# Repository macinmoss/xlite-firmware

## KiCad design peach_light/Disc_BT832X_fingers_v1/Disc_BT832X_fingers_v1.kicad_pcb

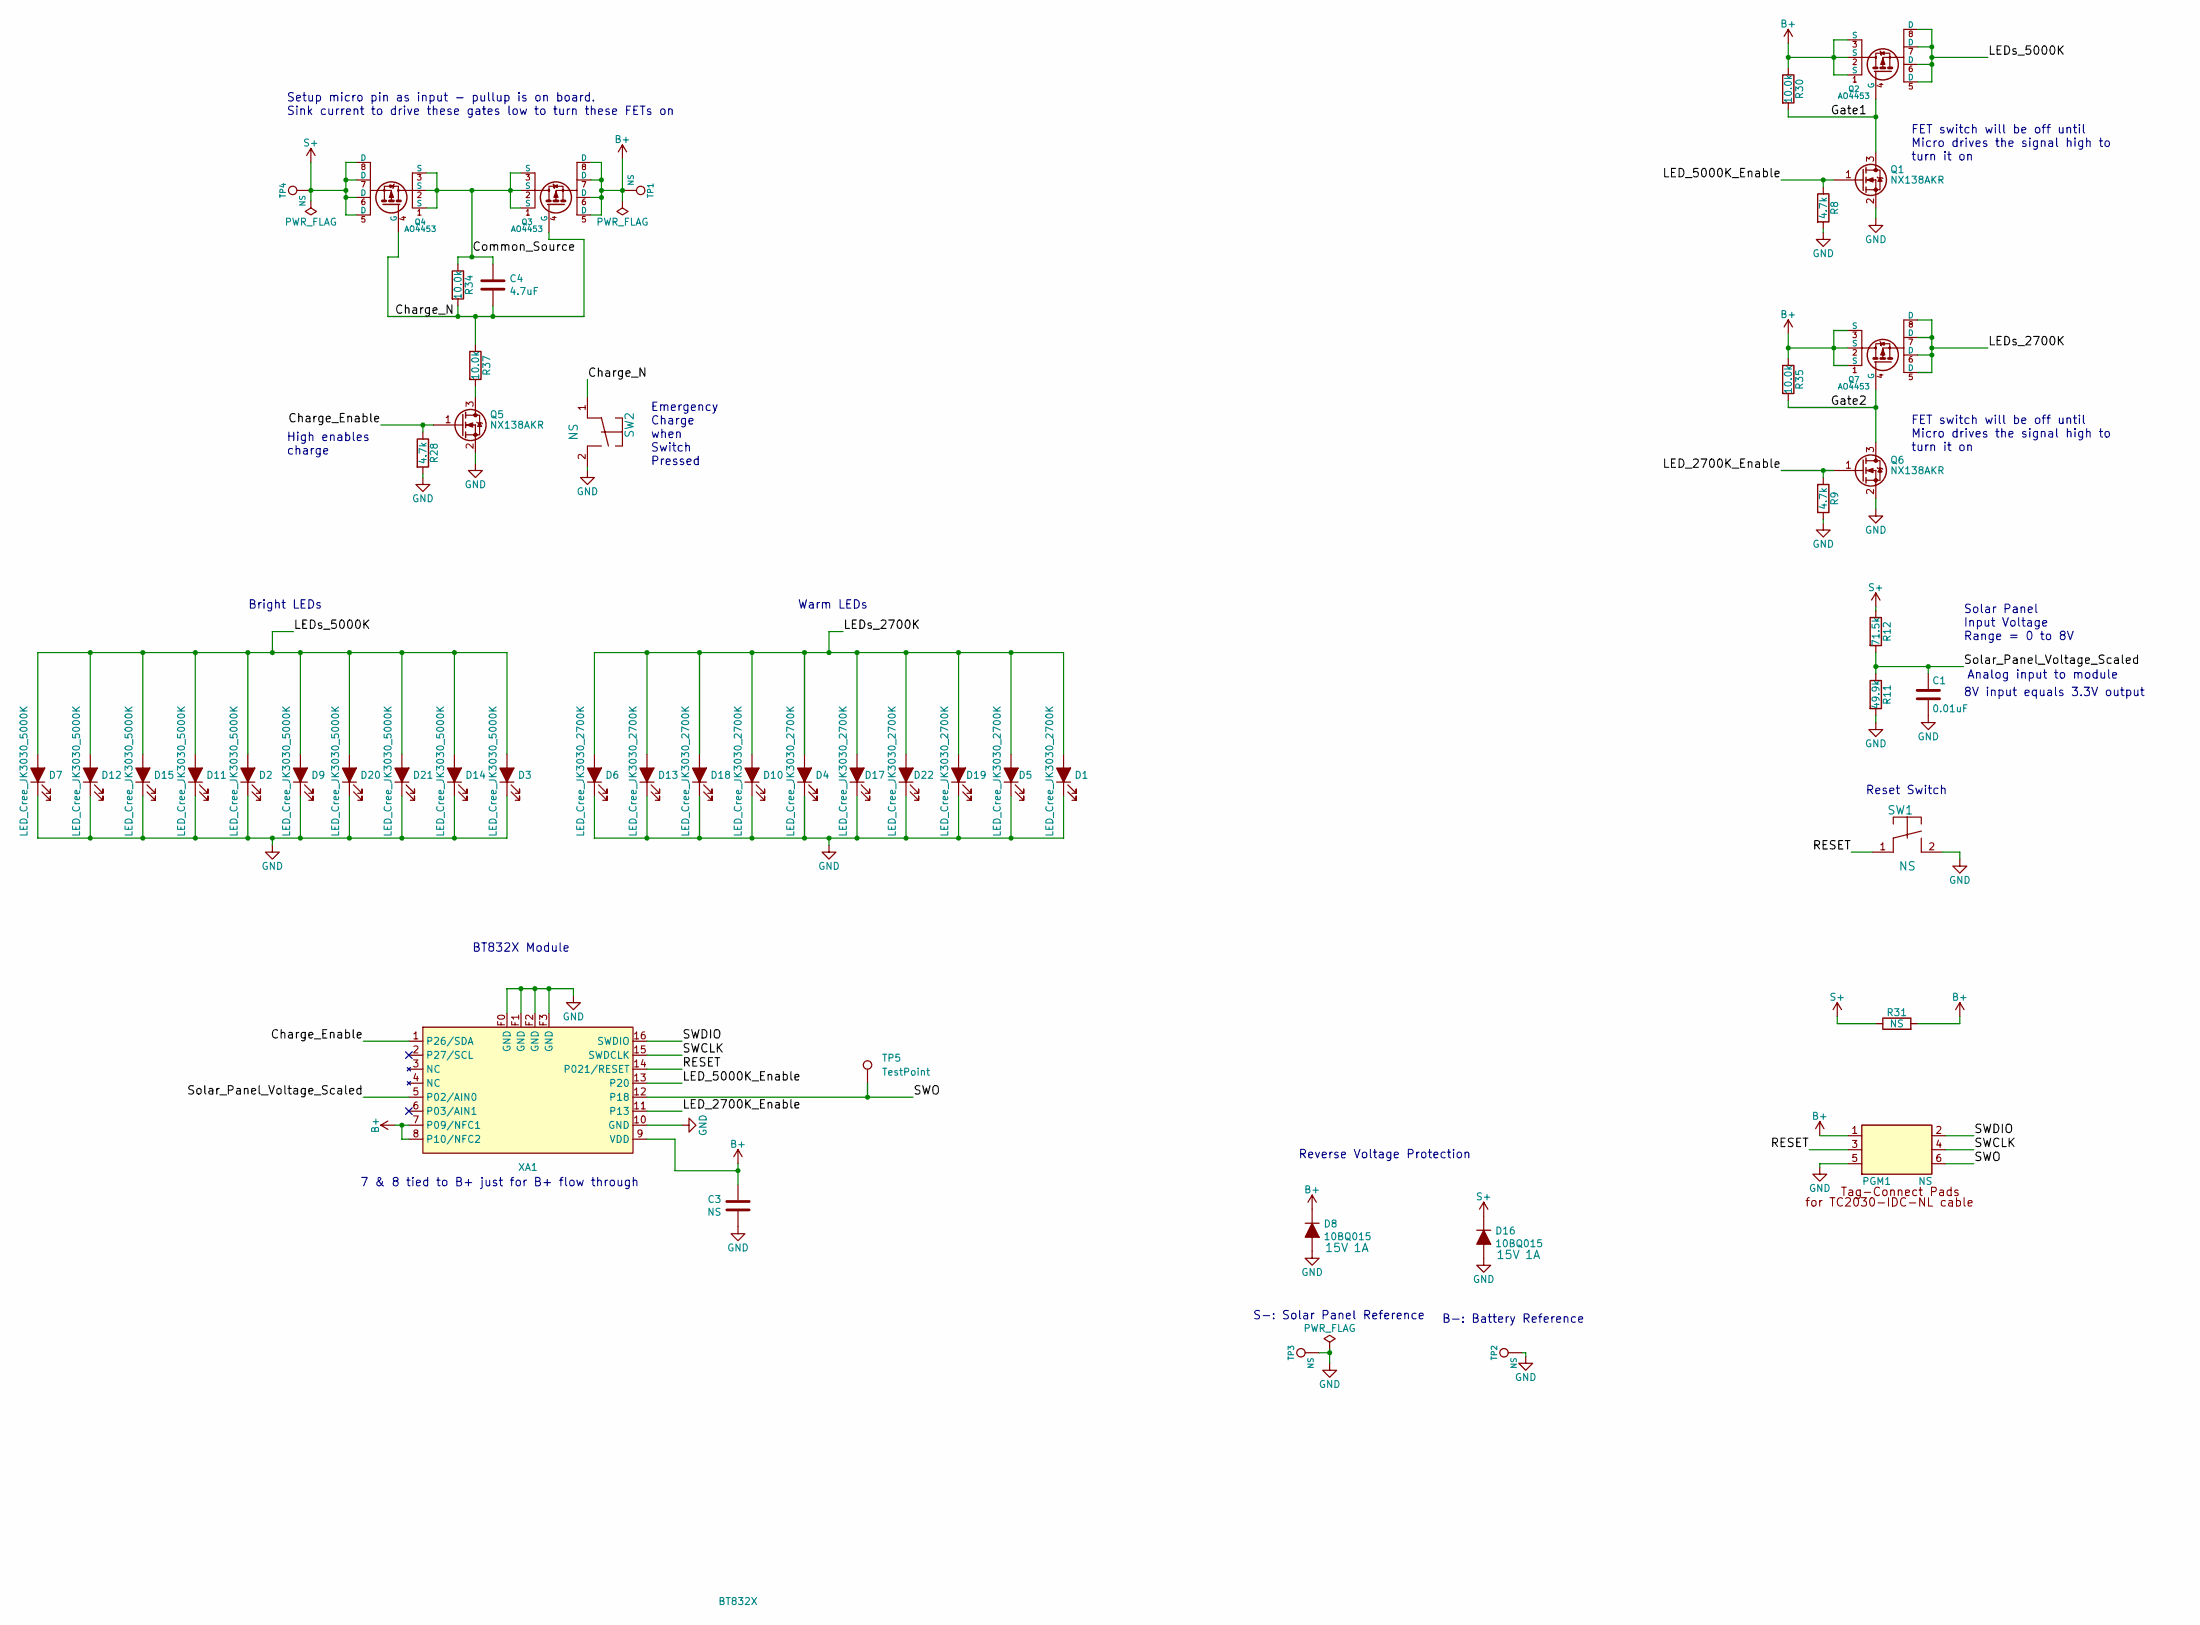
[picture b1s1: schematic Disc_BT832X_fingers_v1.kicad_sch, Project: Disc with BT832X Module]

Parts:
C1: 0.01uF; C_0603_1608Metric; MPN CGA3E2X7R1H103K080AA
C3: NS; C_1206_3216Metric
C4: 4.7uF; C_0805_2012Metric; MPN C2012X7R1A475M125AC
D1, D4, D5, D6, D10, D13, D17, D18, D19, D22: LED_Cree_JK3030_2700K; LED_Cree-J_Series_3030; MPN JK3030AWT-00-0000-000A0HL250E
D2, D3, D7, D9, D11, D12, D14, D15, D20, D21: LED_Cree_JK3030_5000K; LED_Cree-J_Series_3030; MPN JK3030AWT-00-0000-000A0HL250E
D8, D16: 10BQ015; D_SMB; Voltage 15V; MPN 10BQ015
PGM1: NS; PADS_PROGRAMMING_Tag-Connect_TC2030-IDC-NL; MPN None
Q1, Q5, Q6: NX138AKR; SOT-23; MPN NX138AKR
Q2, Q3, Q4, Q7: AO4453; Q_Vishay_Si4465ADY_SOIC-8_3.9x4.9mm_P1.27mm; MPN AO4453
R8, R9, R28: 4.7k; R_0603_1608Metric; MPN RC0603FR-074K7L
R11: 49.9k; R_0603_1608Metric; MPN ERJ-3EKF4992V
R12: 71.5k; R_0603_1608Metric; MPN ERJ-3EKF7152V
R30, R34, R35, R37: 10.0k; R_0603_1608Metric; MPN AC0603FR-0710KL
R31: NS; R_0603_1608Metric; MPN Not_Specified
SW1, SW2: NS; SW_SPST_Omron_B3U-1000P; MPN Not_Specified
TP1, TP2, TP3, TP4: NS; WirePad_2.5mmx2.5mm; MPN Not_Specified
TP5: TestPoint; TestPoint_Pad_04
XA1: BT832X; Fanstel_BT832X_without_BGA

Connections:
/Charge_Enable: Q5.1 (G), R28.1, XA1.1 (P26/SDA)
/Charge_N: C4.2, Q3.4 (G), Q4.4 (G), R34.2, R37.1, SW2.1
/Common_Source: C4.1, Q3.1 (S), Q3.2 (S), Q3.3 (S), Q4.1 (S), Q4.2 (S), Q4.3 (S), R34.1
/Gate1: Q1.3 (D), Q2.4 (G), R30.2
/Gate2: Q6.3 (D), Q7.4 (G), R35.2
/LED_2700K_Enable: Q6.1 (G), R9.1, XA1.11 (P13)
/LED_5000K_Enable: Q1.1 (G), R8.1, XA1.13 (P20)
/LEDs_2700K: D1.2 (A), D4.2 (A), D5.2 (A), D6.2 (A), D10.2 (A), D13.2 (A), D17.2 (A), D18.2 (A), D19.2 (A), D22.2 (A), Q7.5 (D), Q7.6 (D), Q7.7 (D), Q7.8 (D)
/LEDs_5000K: D2.2 (A), D3.2 (A), D7.2 (A), D9.2 (A), D11.2 (A), D12.2 (A), D14.2 (A), D15.2 (A), D20.2 (A), D21.2 (A), Q2.5 (D), Q2.6 (D), Q2.7 (D), Q2.8 (D)
/RESET: PGM1.3, SW1.1, XA1.14 (P021/RESET)
/SWCLK: PGM1.4, XA1.15 (SWDCLK)
/SWDIO: PGM1.2, XA1.16 (SWDIO)
/SWO: PGM1.6, TP5.1, XA1.12 (P18)
/Solar_Panel_Voltage_Scaled: C1.1, R11.1, R12.2, XA1.5 (P02/AIN0)
B+: C3.1, D8.1 (K), PGM1.1, Q2.1 (S), Q2.2 (S), Q2.3 (S), Q3.5 (D), Q3.6 (D), Q3.7 (D), Q3.8 (D), Q7.1 (S), Q7.2 (S), Q7.3 (S), R30.1, R31.2, R35.1, TP1.1, XA1.7 (P09/NFC1), XA1.8 (P10/NFC2), XA1.9 (VDD)
GND: C1.2, C3.2, D1.1 (K), D2.1 (K), D3.1 (K), D4.1 (K), D5.1 (K), D6.1 (K), D7.1 (K), D8.2 (A), D9.1 (K), D10.1 (K), D11.1 (K), D12.1 (K), D13.1 (K), D14.1 (K), D15.1 (K), D16.2 (A), D17.1 (K), D18.1 (K), D19.1 (K), D20.1 (K), D21.1 (K), D22.1 (K), PGM1.5, Q1.2 (S), Q5.2 (S), Q6.2 (S), R8.2, R9.2, R11.2, R28.2, SW1.2, SW2.2, TP2.1, TP3.1, XA1.10 (GND), XA1.F0 (GND), XA1.F1 (GND), XA1.F2 (GND), XA1.F3 (GND)
unnamed: Q5.3 (D), R37.2
S+: D16.1 (K), Q4.5 (D), Q4.6 (D), Q4.7 (D), Q4.8 (D), R12.1, R31.1, TP4.1

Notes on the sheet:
8V input equals 3.3V output
High enables charge
Bright LEDs
Setup micro pin as input - pullup is on board. Sink current to drive these gates low to turn these FETs on
Warm LEDs
7 & 8 tied to B+ just for B+ flow through
Solar Panel Input Voltage Range = 0 to 8V
Analog input to module
S-: Solar Panel Reference
BT832X Module
Reset Switch
B-: Battery Reference
FET switch will be off until Micro drives the signal high to turn it on
Emergency Charge when Switch Pressed
Reverse Voltage Protection

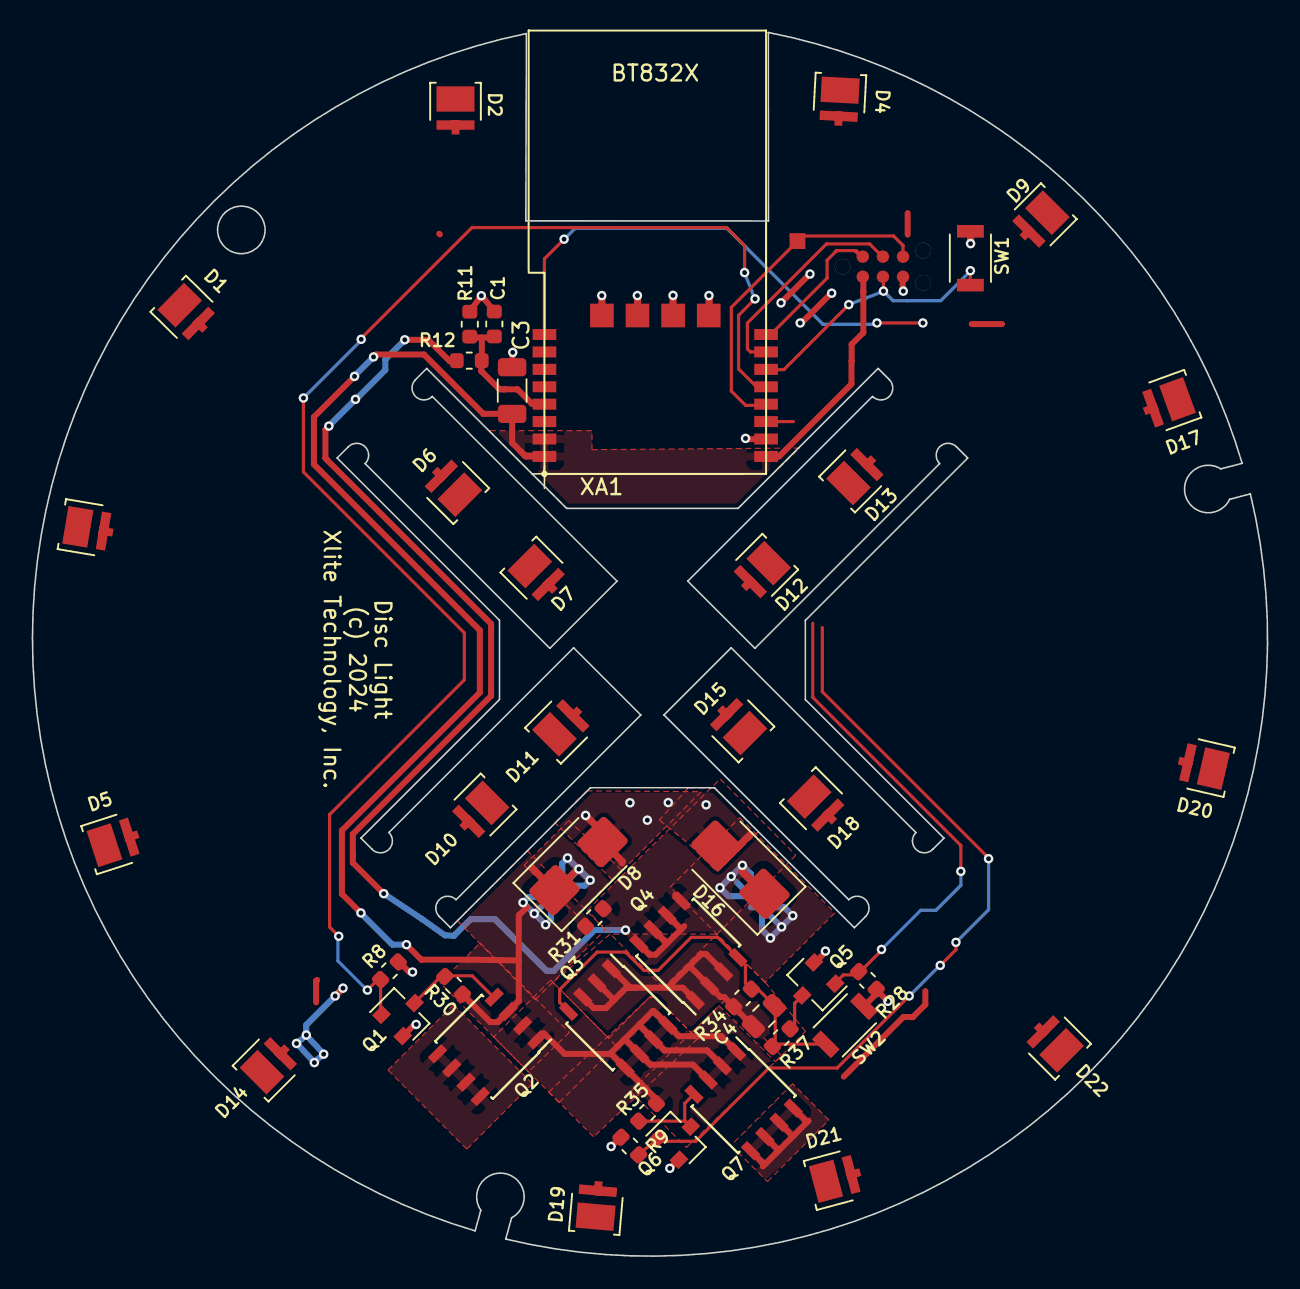
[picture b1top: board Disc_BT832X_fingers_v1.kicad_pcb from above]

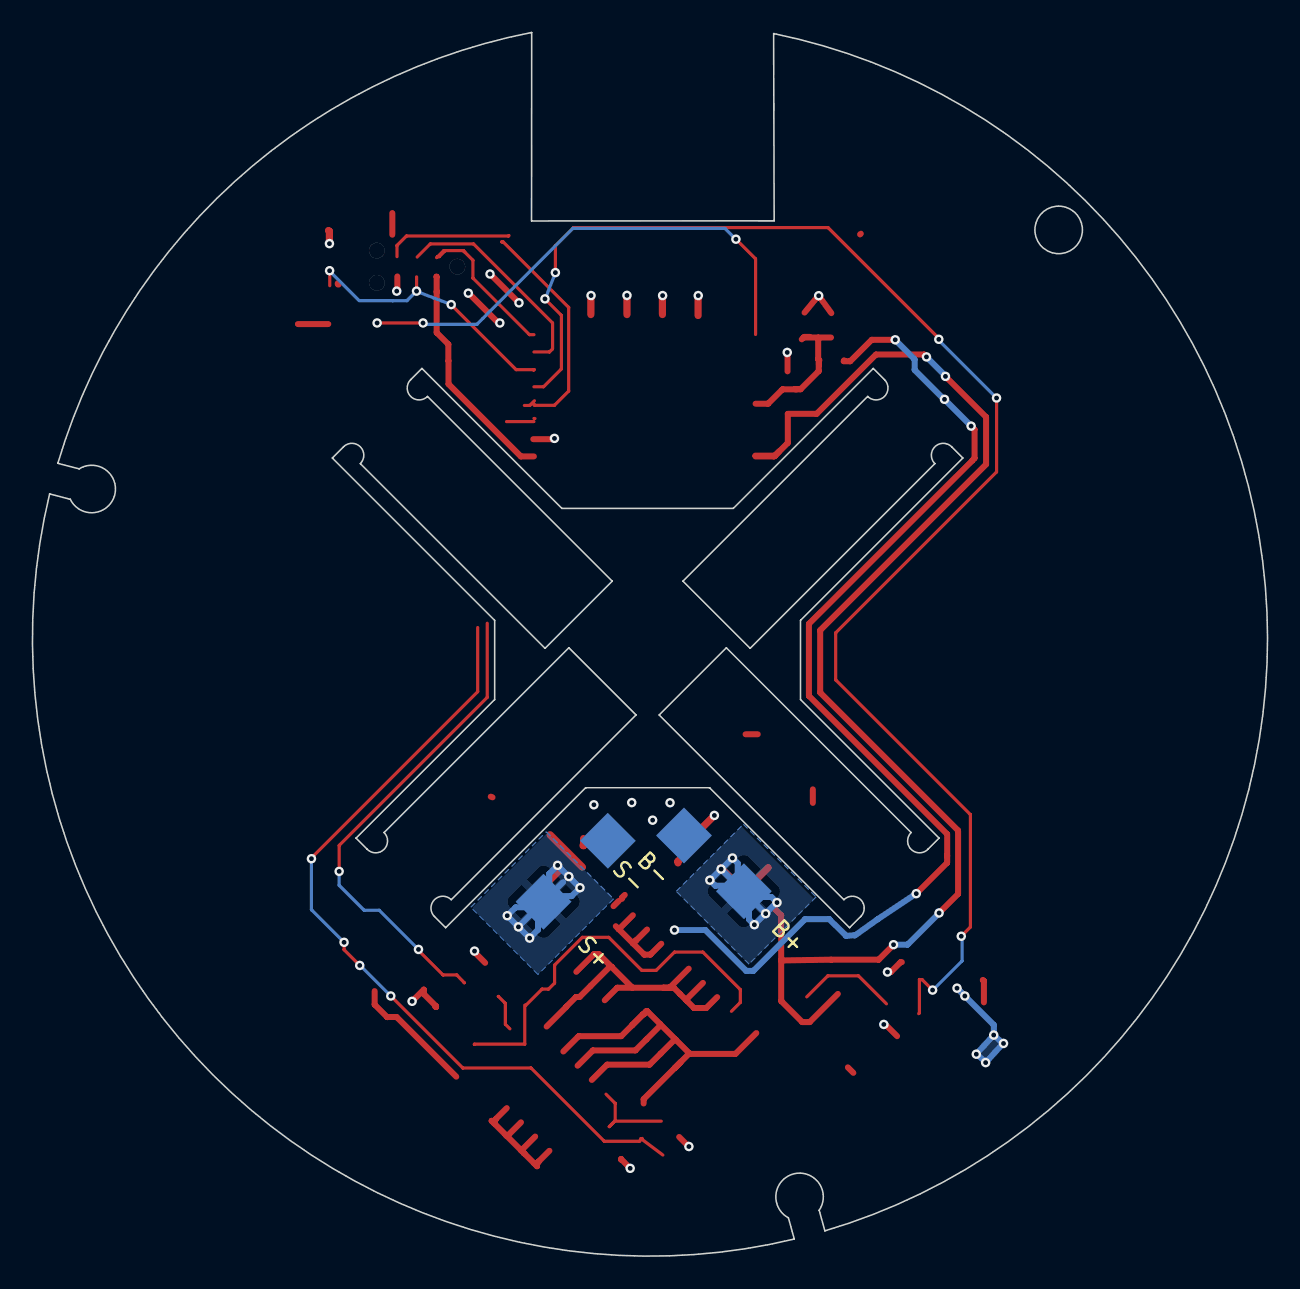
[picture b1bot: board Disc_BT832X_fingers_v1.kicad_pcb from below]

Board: 2 copper layers, 78.0 x 77.3 mm, 51 parts (4 on the bottom side), 18 nets.

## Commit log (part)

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2026-04-22 Bump to v1.0.1 (OTA test)

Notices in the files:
peach_light/Disc_BT832X_fingers_v1/Disc_BT832X_fingers_v1.kicad_pcb:
(c) 2024
